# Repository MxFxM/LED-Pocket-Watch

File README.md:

# LED-Pocket-Watch
 I build a LED watch in the case of a broken pocket watch

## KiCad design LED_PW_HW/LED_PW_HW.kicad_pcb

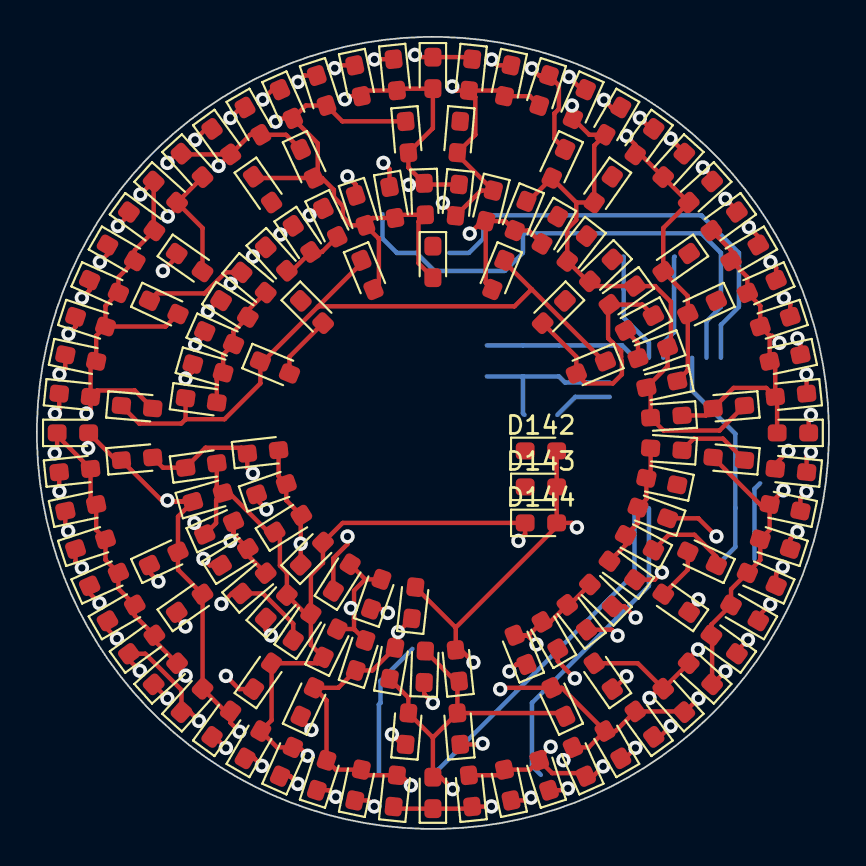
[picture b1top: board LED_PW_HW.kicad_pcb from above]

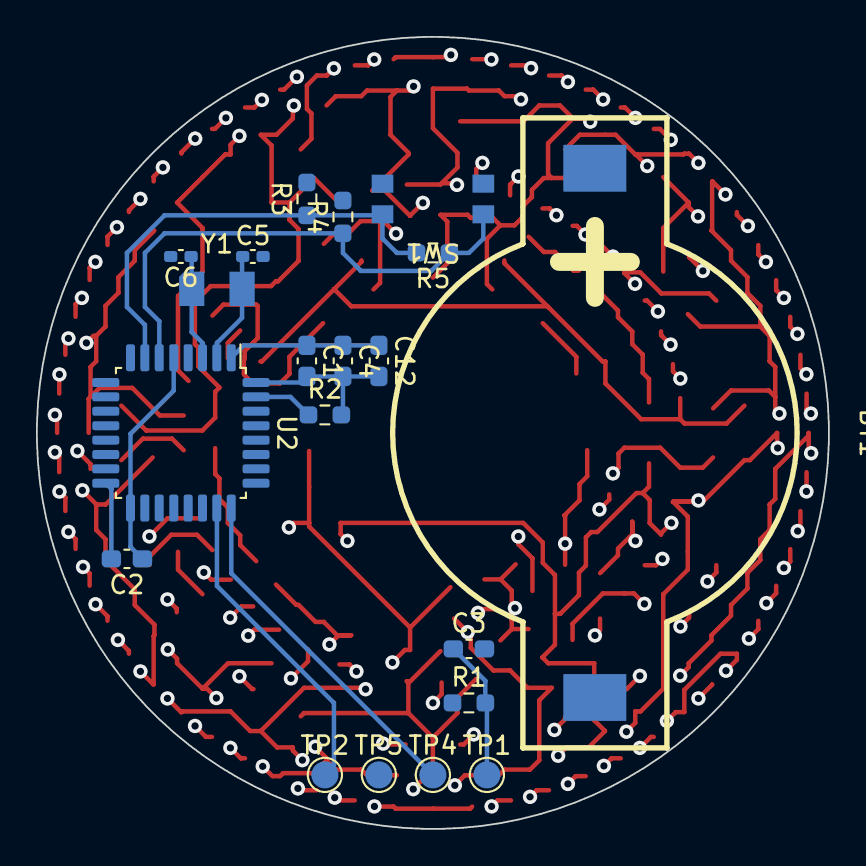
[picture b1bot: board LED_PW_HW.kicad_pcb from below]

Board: 4 copper layers, 44.0 x 44.0 mm, 164 parts (20 on the bottom side), 28 nets.

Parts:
BT1: Battery_Holder; SMTU2032-LF
C1, C2, C3: 100n; C_0603_1608Metric_Pad1.08x0.95mm_HandSolder
C4: 1u; C_0603_1608Metric_Pad1.08x0.95mm_HandSolder
C5, C6: 4p3; C_0402_1005Metric_Pad0.74x0.62mm_HandSolder
C12: 100n n.b.; C_0603_1608Metric_Pad1.08x0.95mm_HandSolder
D1, D2, D3, D4, D5, D6, D7, D8, D9, D10, D11, D12, D13, D14, D15, D16, D17, D18, D19, D20, D21, D22, D23, D24, D25, D26, D27, D28, D29, D30, D31, D32, D33, D34, D35, D36, D37, D38, D39, D40, D41, D42, D43, D44, D45, D46, D47, D48, D49, D50, D51, D52, D53, D54, D55, D56, D57, D58, D59, D60, D61, D62, D63, D64, D65, D66, D67, D68, D69, D70, D71, D72, D73, D74, D75, D76, D77, D78, D79, D80, D81, D82, D83, D84, D85, D86, D87, D88, D89, D90, D91, D92, D93, D94, D95, D96, D97, D98, D99, D100, D101, D102, D103, D104, D105, D106, D107, D108, D109, D110, D111, D112, D113, D114, D115, D116, D117, D118, D119, D120, D121, D122, D123, D124, D125, D126, D127, D128, D129, D130, D131, D132, D133, D134, D135, D136, D137, D138, D139, D140, D141, D142, D143, D144: LED; LED_0603_1608Metric_Pad1.05x0.95mm_HandSolder
R1, R2, R3, R4: 100k; R_0603_1608Metric_Pad0.98x0.95mm_HandSolder
R5: n.b.; R_0603_1608Metric_Pad0.98x0.95mm_HandSolder
SW1: SW_MEC_5E; Switch-DifferentPadNr
TP1, TP2, TP4, TP5: TestPoint; TestPoint_Pad_D1.5mm
U2: STM32L031K6Tx; LQFP-32_7x7mm_P0.8mm
Y1: Crystal; ECX-34Q

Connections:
+3V3: BT1.1 (+), C1.1, C2.1, C4.1, C12.1, R1.1, SW1.3 (K), SW1.4 (A), U2.1 (VDD), U2.5 (VDDA), U2.17 (VDD)
BOOT: R2.1, U2.31 (BOOT0)
BTN_IN: R3.1, R5.2, SW1.1, U2.7 (PA1)
CA1: D32.2 (A), D33.2 (A), D34.2 (A), D35.2 (A), D36.2 (A), D37.2 (A), D38.1 (K), D41.1 (K), D43.1 (K), D46.1 (K), D47.1 (K), D50.1 (K), D52.1 (K), D55.1 (K), D67.2 (A), D80.2 (A)
CA2: D37.1 (K), D38.2 (A), D39.2 (A), D40.1 (K), D42.1 (K), D45.1 (K), D48.1 (K), D51.1 (K), D53.1 (K), D56.1 (K), D68.2 (A), D86.2 (A), D87.2 (A), D88.2 (A), D89.2 (A), D90.2 (A)
CA3: D36.1 (K), D39.1 (K), D40.2 (A), D41.2 (A), D44.1 (K), D49.1 (K), D54.1 (K), D57.1 (K), D69.1 (K), D81.2 (A), D83.1 (K), D91.2 (A), D92.2 (A), D93.2 (A), D117.2 (A), D130.2 (A)
CA4: D35.1 (K), D42.2 (A), D43.2 (A), D58.1 (K), D68.1 (K), D69.2 (A), D70.1 (K), D71.1 (K), D81.1 (K), D82.1 (K), D84.1 (K), D94.2 (A), D95.2 (A), D96.2 (A), D131.2 (A), D132.2 (A)
CA5: D44.2 (A), D45.2 (A), D46.2 (A), D59.1 (K), D72.1 (K), D80.1 (K), D82.2 (A), D90.1 (K), D93.1 (K), D96.1 (K), D97.1 (K), D98.2 (A), D99.2 (A), D100.2 (A), D101.1 (K), D133.2 (A)
CA6: D34.1 (K), D47.2 (A), D48.2 (A), D49.2 (A), D60.1 (K), D70.2 (A), D89.1 (K), D92.1 (K), D95.1 (K), D97.2 (A), D98.1 (K), D102.1 (K), D103.2 (A), D104.1 (K), D134.2 (A), D135.2 (A)
CA7: D33.1 (K), D50.2 (A), D51.2 (A), D71.2 (A), D73.1 (K), D83.2 (A), D88.1 (K), D91.1 (K), D94.1 (K), D99.1 (K), D101.2 (A), D102.2 (A), D103.1 (K), D105.1 (K), D106.2 (A), D107.2 (A)
CA8: D1.1 (K), D2.2 (A), D32.1 (K), D52.2 (A), D53.2 (A), D54.2 (A), D72.2 (A), D84.2 (A), D87.1 (K), D100.1 (K), D104.2 (A), D105.2 (A), D106.1 (K), D130.1 (K), D132.1 (K), D134.1 (K)
CA9: D1.2 (A), D2.1 (K), D55.2 (A), D56.2 (A), D57.2 (A), D58.2 (A), D59.2 (A), D60.2 (A), D67.1 (K), D73.2 (A), D86.1 (K), D107.1 (K), D117.1 (K), D131.1 (K), D133.1 (K), D135.1 (K)
CB1: D24.2 (A), D25.2 (A), D26.2 (A), D27.2 (A), D28.2 (A), D29.2 (A), D30.2 (A), D31.1 (K), D61.1 (K), D79.2 (A), D108.1 (K), D113.1 (K), D129.1 (K), D137.1 (K), D141.1 (K), D142.1 (K)
CB2: D3.1 (K), D22.2 (A), D23.2 (A), D31.2 (A), D66.2 (A), D78.2 (A), D79.1 (K), D109.1 (K), D114.1 (K), D125.2 (A), D126.2 (A), D127.2 (A), D128.1 (K), D136.1 (K), D140.1 (K), D143.1 (K)
CB3: D4.1 (K), D20.2 (A), D21.2 (A), D30.1 (K), D65.2 (A), D110.1 (K), D115.1 (K), D122.1 (K), D123.2 (A), D124.2 (A), D127.1 (K), D128.2 (A), D129.2 (A), D138.2 (A), D139.1 (K), D144.1 (K)
CB4: D17.2 (A), D18.2 (A), D19.2 (A), D29.1 (K), D74.1 (K), D77.2 (A), D85.1 (K), D111.1 (K), D116.1 (K), D120.2 (A), D121.1 (K), D126.1 (K), D138.1 (K), D139.2 (A), D140.2 (A), D141.2 (A)
CB5: D5.1 (K), D16.2 (A), D28.1 (K), D63.1 (K), D64.2 (A), D66.1 (K), D76.2 (A), D112.1 (K), D118.1 (K), D119.2 (A), D120.1 (K), D121.2 (A), D122.2 (A), D124.1 (K), D136.2 (A), D137.2 (A)
CB6: D12.1 (K), D13.2 (A), D14.2 (A), D15.2 (A), D27.1 (K), D62.1 (K), D75.1 (K), D77.1 (K), D85.2 (A), D118.2 (A), D119.1 (K), D123.1 (K), D125.1 (K), D142.2 (A), D143.2 (A), D144.2 (A)
CB7: D6.1 (K), D9.1 (K), D10.2 (A), D11.2 (A), D12.2 (A), D13.1 (K), D19.1 (K), D26.1 (K), D63.2 (A), D64.1 (K), D65.1 (K), D78.1 (K), D113.2 (A), D114.2 (A), D115.2 (A), D116.2 (A)
CB8: D7.1 (K), D8.2 (A), D9.2 (A), D10.1 (K), D14.1 (K), D18.1 (K), D21.1 (K), D23.1 (K), D25.1 (K), D75.2 (A), D76.1 (K), D108.2 (A), D109.2 (A), D110.2 (A), D111.2 (A), D112.2 (A)
CB9: D3.2 (A), D4.2 (A), D5.2 (A), D6.2 (A), D7.2 (A), D8.1 (K), D11.1 (K), D15.1 (K), D16.1 (K), D17.1 (K), D20.1 (K), D22.1 (K), D24.1 (K), D61.2 (A), D62.2 (A), D74.2 (A)
GND: BT1.2 (-), C1.2, C2.2, C3.2, C4.2, C5.2, C6.2, C12.2, R2.2, R3.2, R4.2, TP5.1, U2.16 (VSS), U2.32 (VSS)
RCC_OSC32_IN: C5.1, U2.2 (PC14), Y1.2
RCC_OSC32_OUT: C6.1, U2.3 (PC15), Y1.1
RESET: C3.1, R1.2, TP1.1, U2.4 (NRST)
SWCLK: TP4.1, U2.24 (PA14)
SWDIO: TP2.1, U2.23 (PA13)
SYS_WKUP1: R4.1, R5.1, SW1.2, U2.6 (PA0)

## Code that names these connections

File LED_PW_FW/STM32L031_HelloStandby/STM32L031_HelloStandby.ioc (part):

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Mcu.Name=STM32L031K(4-6)Tx
Mcu.Package=LQFP32
Mcu.UserName=STM32L031K6Tx
PA0-CK_IN.Mode=SYS_WakeUp0
PA0-CK_IN.Signal=SYS_WKUP1
PA1.GPIOParameters=GPIO_PuPd
PA1.GPIO_PuPd=GPIO_PULLDOWN
PA1.Signal=GPIO_Input
PA13.GPIOParameters=GPIO_Label
PA13.GPIO_Label=TMS
PA13.Mode=Serial_Wire
PA13.Signal=SYS_SWDIO
PA14.GPIOParameters=GPIO_Label
PA14.GPIO_Label=TCK
PA14.Mode=Serial_Wire
PA14.Signal=SYS_SWCLK
PA15.GPIOParameters=GPIO_Label
PA15.GPIO_Label=VCP_RX
PA15.Mode=Asynchronous
PA15.Signal=USART2_RX
PA2.GPIOParameters=GPIO_Label
PA2.GPIO_Label=VCP_TX
PA2.Mode=Asynchronous
PA2.Signal=USART2_TX
PB3.GPIOParameters=GPIO_Label
PB3.GPIO_Label=LD3 [Green]
PB3.Signal=GPIO_Output
PC14-OSC32_IN.Mode=LSE-External-Oscillator
PC14-OSC32_IN.Signal=RCC_OSC32_IN
PC15-OSC32_OUT.Mode=LSE-External-Oscillator
PC15-OSC32_OUT.Signal=RCC_OSC32_OUT
RCC.HSE_VALUE=8000000
RCC.SYSCLKFreq_VALUE=32000000
RCC.SYSCLKSource=RCC_SYSCLKSOURCE_PLLCLK
board=NUCLEO-L031K6
boardIOC=true

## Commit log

2022-01-01 created kicad project for hardware
2022-01-01 casing measurements
2022-01-01 created footprints for battery holder and led driver
2022-01-01 led matrix as in datasheet of driver
2022-01-01 created footprint for battery holder and led driver
2022-01-01 imported first footprints to pcb to get an idea
2022-01-02 experimenting with plugin
2022-01-02 sorting the leds
2022-01-02 sorted leds
2022-01-03 hello world with rtc on stm32l031k6 nucleo
2022-01-04 tests with standby
2022-01-04 i2c test
2022-01-04 combination of all tests for a final test
2022-01-06 schematic of led driver part done
2022-01-06 controller schematic part done
2022-01-06 led placement
2022-01-06 giving up for now and going with 72 leds
2022-01-11 backup changes
2022-01-11 changes on date compilation
2022-01-11 new version
2022-01-15 v3 is a cleaner v1
2022-01-20 hey, v1 actually runs
    but not on a button cell, because the led driver needs higher voltage. i use a lipo cell with a diode to drop the voltge by 0.7v
